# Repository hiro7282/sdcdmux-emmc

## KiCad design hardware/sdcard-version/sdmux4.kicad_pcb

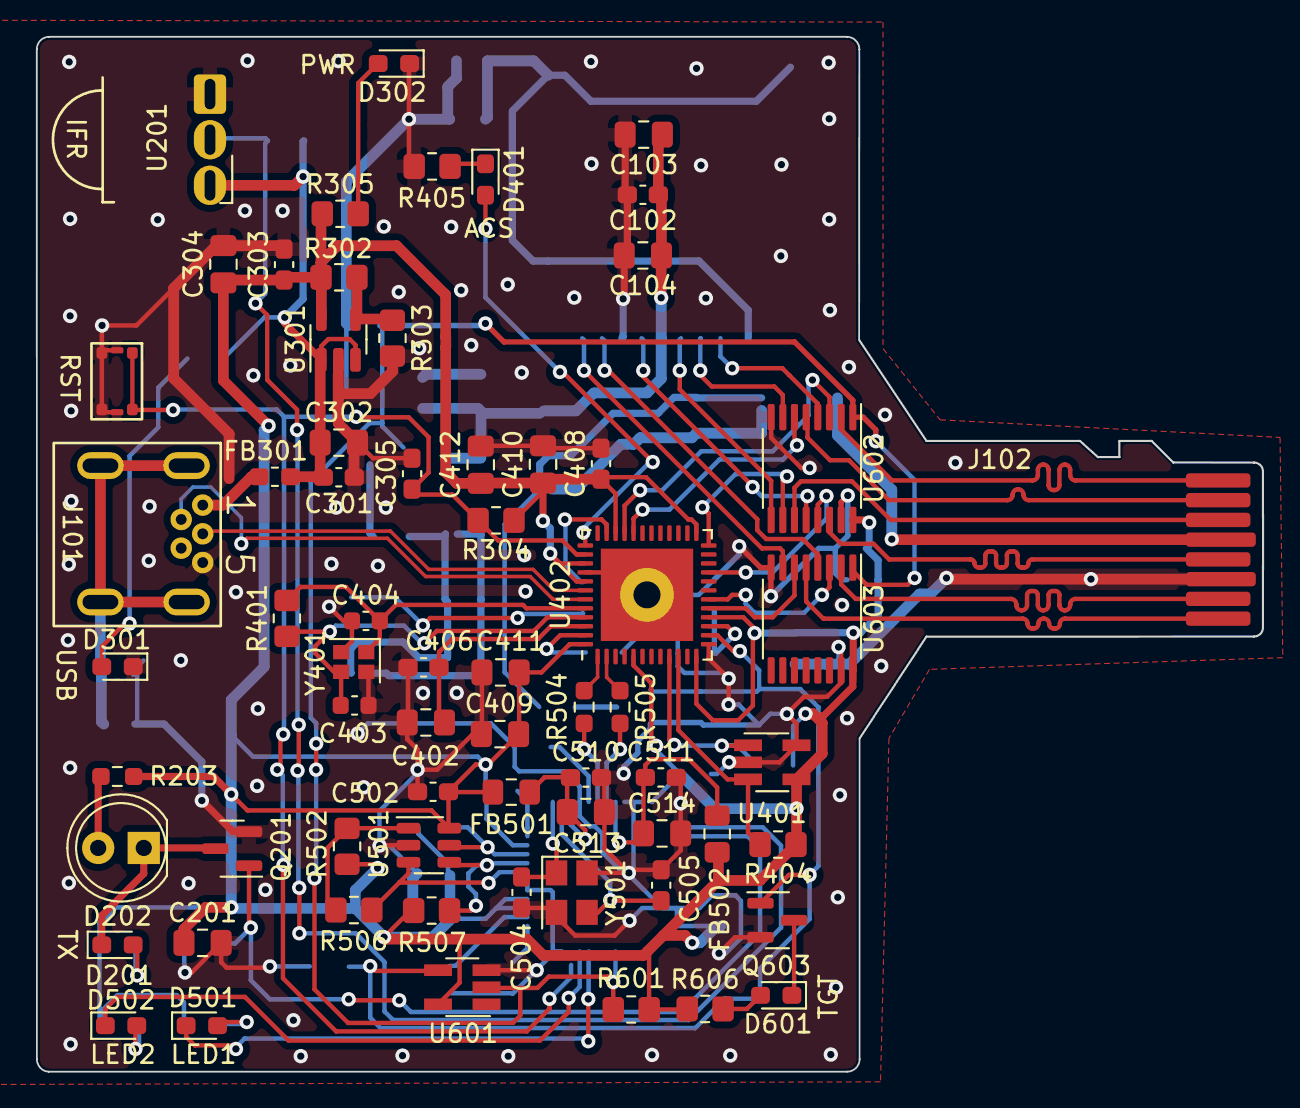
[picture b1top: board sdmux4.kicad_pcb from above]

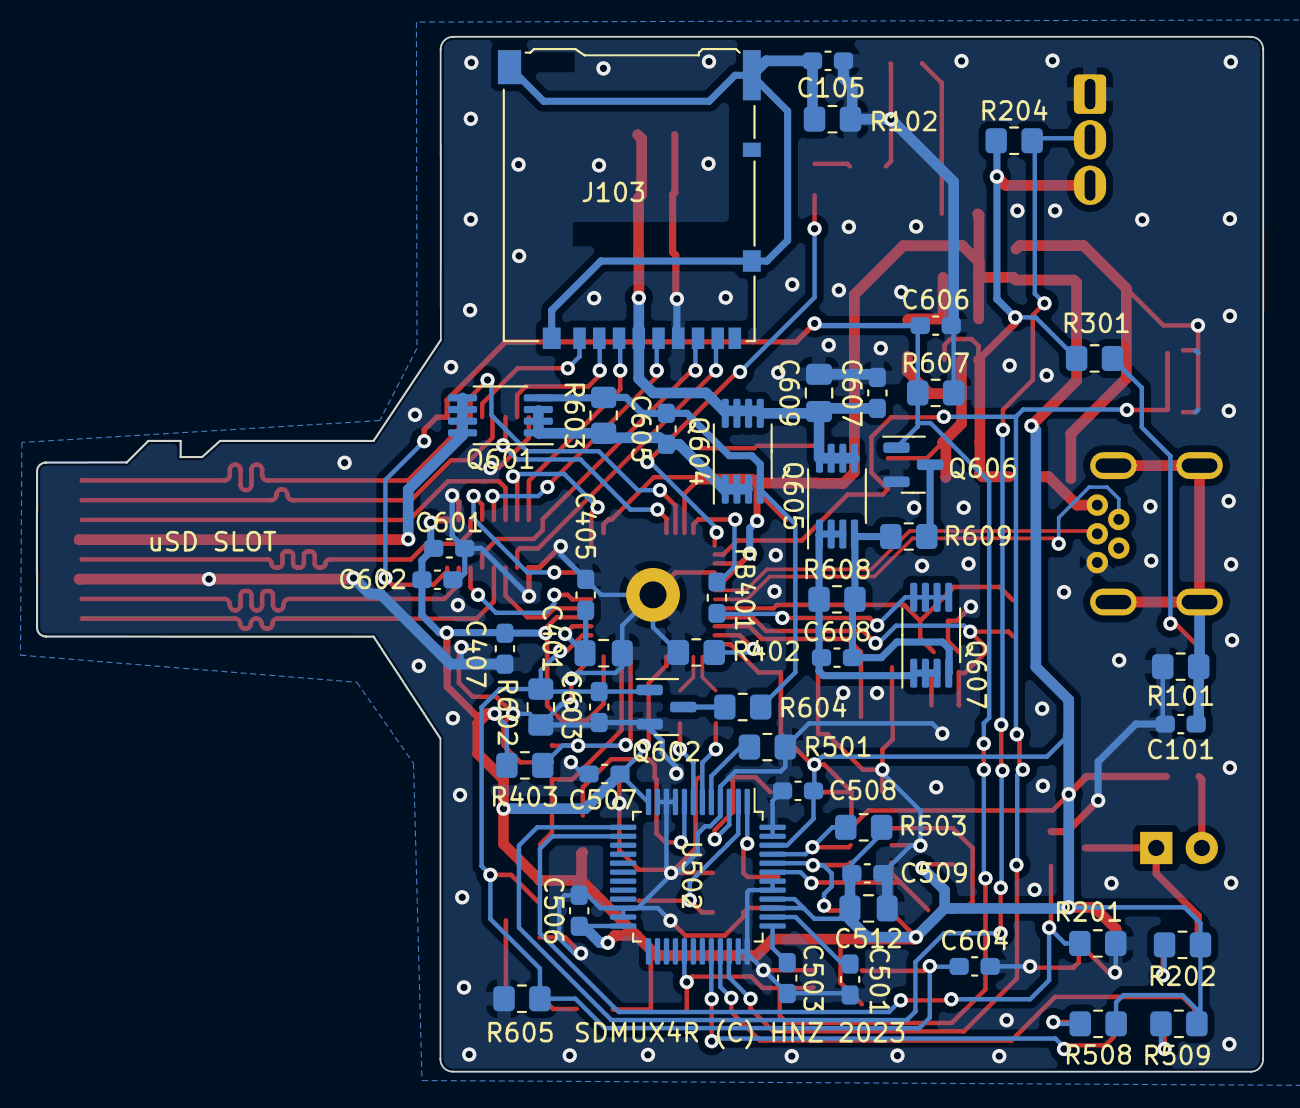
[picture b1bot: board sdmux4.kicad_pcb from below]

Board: 2 copper layers, 68.3 x 57.7 mm, 115 parts (49 on the bottom side), 77 nets.

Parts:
C101, C102, C105, C301, C303, C305, C405, C406, C407, C408, C501, C502, C503, C506, C507, C508, C509, C510, C511, C601, C602, C603, C604, C606, C607: 0.1uF/50v; C_0603_1608Metric_Pad1.08x0.95mm_HandSolder
C103, C401, C402, C409, C410: 1uF/10v; C_0805_2012Metric_Pad1.18x1.45mm_HandSolder
C104, C411, C412, C512, C513, C514: 4.7uF/50v; C_0805_2012Metric_Pad1.18x1.45mm_HandSolder
C201, C302, C304, C609: 10uF/16v; C_0805_2012Metric_Pad1.18x1.45mm_HandSolder
C403, C404: 27pF/50v; C_0603_1608Metric
C504, C505: 27pF/50v; C_0603_1608Metric_Pad1.08x0.95mm_HandSolder
C605, C608: 2.2uF/16v; C_0603_1608Metric_Pad1.08x0.95mm_HandSolder
D201, D301, D302, D401: LED RED; LED_0603_1608Metric_Pad1.05x0.95mm_HandSolder
D202: OSI5LA5113A; LED_D5.0mm
D501: IND-1 LED GRN; LED_0603_1608Metric_Pad1.05x0.95mm_HandSolder
D502: IND-2 LED GRN; LED_0603_1608Metric_Pad1.05x0.95mm_HandSolder
D601: TGT SEL LED RED; LED_0603_1608Metric_Pad1.05x0.95mm_HandSolder
FB301: BLM18KG601SN1D; L_0603_1608Metric_Pad1.05x0.95mm_HandSolder
FB401: BLM18RK102SN1; L_0603_1608Metric_Pad1.05x0.95mm_HandSolder
FB501, FB502: BK2125HS601-T; L_0805_2012Metric_Pad1.15x1.40mm_HandSolder
J101: USB_B_Mini; usb mini B connector c2235 dim 2
J102: uSD-CARD-PAD; uSD Card Pad
J103: Micro_SD_Card_Det_Hirose_DM3AT-SF-PEJM5; microSD_HC_Hirose_DM3AT-SF-PEJM5
Q201, Q602, Q603, Q606: 2N7002K; SOT-23
Q601, Q604, Q605, Q607: ZXM64P02XTA; MSOP-8_3x3mm_P0.65mm
R101, R102, R201, R204, R304, R403, R404, R502, R503, R507, R601, R602, R603, R605, R607, R608: 10K; R_0805_2012Metric_Pad1.20x1.40mm_HandSolder
R202, R301, R604, R606, R609: 1K; R_0805_2012Metric_Pad1.20x1.40mm_HandSolder
R203: 33R; R_0603_1608Metric_Pad0.98x0.95mm_HandSolder
R302: 20K 1%; R_0805_2012Metric_Pad1.20x1.40mm_HandSolder
R303, R402, R501: 12K 1%; R_0805_2012Metric_Pad1.20x1.40mm_HandSolder
R305: 330; R_0805_2012Metric_Pad1.20x1.40mm_HandSolder
R401: 1M; R_0805_2012Metric_Pad1.20x1.40mm_HandSolder
R405: 330R; R_0805_2012Metric_Pad1.20x1.40mm_HandSolder
R504, R505: 27R; R_0603_1608Metric_Pad0.98x0.95mm_HandSolder
R506: 2K; R_0805_2012Metric_Pad1.20x1.40mm_HandSolder
R508, R509: 220; R_0805_2012Metric_Pad1.20x1.40mm_HandSolder
SW301: 435151014824; WS-TASV SMT Tact Switch
U201: SPS-445; SPS445 3pin
U301: SPX3819M5-L; SOT-23-5
U401: AT24MAC402-STUM; SOT-23-5_HandSoldering
U402: USB2640-HZH-02; QFN-48-1EP_7x7mm_P0.5mm_EP5.15x5.15mm
U501: 93LCxxBxxOT; SOT-23-6
U502: FT232HL; LQFP-48_7x7mm_P0.5mm
U601: 74AHC1G14; SOT-23-5_HandSoldering
U602, U603: TMUX1574PWR; TSSOP-16_4.4x5mm_P0.65mm
Y401: 24MHz; Crystal_SMD_2016-4Pin_2.0x1.6mm
Y501: 12MHz; Crystal_SMD_3225-4Pin_3.2x2.5mm

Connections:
+3.3V: C201.1, C303.1, C304.1, C407.1, C408.1, C409.1, C410.1, C411.1, C412.1, C502.1, C506.1, C507.1, C508.1, C509.1, C512.1, C601.1, C602.1, FB501.1, FB502.1, R202.1, R203.1, R302.1, R304.1, R305.1, R403.1, R404.1, R502.1, R503.1, R507.1, R508.1, R509.1, R601.1, R606.1, U301.5 (OUT), U401.4 (VCC), U402.5 (VDD33), U402.12 (VDD33), U402.16 (VDD33), U402.25 (VDD33), U402.34 (VDD33), U402.39 (VBUS_DET), U402.41 (VDD33), U402.48 (VDD33), U501.6 (VCC), U502.12 (VCCIO), U502.24 (VCCIO), U502.39 (VCCD), U502.40 (VREGIN), U502.46 (VCCIO), U601.5 (VCC), U602.16 (VDD), U603.16 (VDD)
+5V: C301.1, C302.1, FB301.2, R204.1, R301.1, U201.3 (Vcc), U301.1 (IN), U301.3 (EN)
/Infrad Cont/INFRAD_RX: R204.2, U201.2 (Out), U502.13 (ADBUS0)
/Infrad Cont/INFRAD_TX: Q201.1 (G), R201.1, U502.14 (ADBUS1)
/SDCARD_READER/SD1: U402.33 (xD_D5/SD_D2), U602.3 (S1B)
/SDCARD_READER/SD2: U402.32 (xD_D6/SD_D3/MS_D3), U602.6 (S2B)
/SDCARD_READER/SD3: U402.24 (xD_CLE/SD_CMD/MS_D0), U602.10 (S3B)
/SDCARD_READER/SD4: FB401.2, Q607.5 (D), Q607.6 (D), Q607.7 (D), Q607.8 (D)
/SDCARD_READER/SD5: U402.21 (xD_nWP/SD_CLK/MS_BS), U602.13 (S4B)
/SDCARD_READER/SD7: U402.18 (xD_D2/SD_D0/MS_D4), U603.3 (S1B)
/SDCARD_READER/SD8: U402.17 (xD_D3/SD_D1/MS_D5), U603.6 (S2B)
/SDCARD_READER/SD9: C603.1, C604.1, Q602.1 (G), Q603.1 (G), R602.1, R605.1, U402.14 (SD_~CD), U601.4
/SDCARD_READER/USB+: J101.3 (D+), U402.42 (USB+)
/SDCARD_READER/USB-: J101.2 (D-), U402.43 (USB-)
/SDCARD_READER/USBDP1+: R505.1, U402.2 (USBDN_DP2)
/SDCARD_READER/USBDP1-: R504.1, U402.1 (USBDN_DM2)
/SDCARD_READER/~RESET: C305.1, R304.2, SW301.1, SW301.2, U402.38 (~RESET), U502.34 (~RESET)
/SDMUX/SD1_1: J102.1, U602.2 (S1A)
/SDMUX/SD1_2: J102.2, U602.5 (S2A)
/SDMUX/SD1_3: J102.3, U602.11 (S3A)
/SDMUX/SD1_4: J102.4, Q601.5 (D), Q601.6 (D), Q601.7 (D), Q601.8 (D)
/SDMUX/SD1_5: J102.5, U602.14 (S4A)
/SDMUX/SD1_7: J102.7, U603.2 (S1A)
/SDMUX/SD1_8: J102.8, U603.5 (S2A)
/SDMUX/SDOUT1: J103.1 (DAT2), U602.4 (D1)
/SDMUX/SDOUT2: J103.2 (DAT3/CD), U602.7 (D2)
/SDMUX/SDOUT3: J103.3 (CMD), U602.9 (D3)
/SDMUX/SDOUT4: C102.1, C103.1, C104.1, C607.1, C609.1, J103.4 (VDD), Q604.5 (D), Q604.6 (D), Q604.7 (D), Q604.8 (D), Q605.5 (D), Q605.6 (D), Q605.7 (D), Q605.8 (D)
/SDMUX/SDOUT5: J103.5 (CLK), U602.12 (D4)
/SDMUX/SDOUT7: J103.7 (DAT0), U603.4 (D1)
/SDMUX/SDOUT8: J103.8 (DAT1), U603.7 (D2)
/SDMUX/~SEL1: C606.1, Q606.1 (G), R601.2, R607.1, U502.29 (ACBUS5), U601.2, U602.1 (SEL), U603.1 (SEL)
/SELECTOR/ACBUS8: D501.1 (K), U502.32 (ACBUS8)
/SELECTOR/ACBUS9: D502.1 (K), U502.33 (ACBUS9)
/SELECTOR/VPHY: C510.1, C513.1, FB501.2, U502.3 (VPHY)
/SELECTOR/VPLL: C511.1, C514.1, FB502.2, U502.8 (VPLL)
/USB Power/USBVDD_5V: FB301.1, J101.1 (VBUS)
GND: C101.2, C102.2, C103.2, C104.2, C105.2, C201.2, C301.2, C302.2, C303.2, C304.2, C305.2, C401.2, C402.2, C403.1, C404.1, C405.2, C406.2, C407.2, C408.2, C409.2, C410.2, C411.2, C412.2, C501.2, C502.2, C503.2, C504.2, C505.2, C506.2, C507.2, C508.2, C509.2, C510.2, C511.2, C512.2, C513.2, C514.2, C601.2, C602.2, C603.2, C604.2, C606.2, C607.2, C609.2, D301.1 (K), D302.1 (K), J101.5 (GND), J102.6, J103.6 (VSS), Q201.2 (S), Q602.2 (S), Q603.2 (S), Q606.2 (S), R101.2, R102.2, R201.2, R303.2, R402.2, R405.2, R501.2, R602.2, R605.2, R607.2, SW301.3 (K), SW301.4 (A), SW301.5, SW301.6, U201.1 (GND), U301.2 (GND), U401.2 (GND), U401.5 (WP), U402.13 (xD_D4/SD_WP/MS_SCLK), U402.40 (TEST), U402.49 (VSS), U501.2 (GND), U502.4 (AGND), U502.9 (AGND), U502.10 (GND), U502.11 (GND), U502.22 (GND), U502.23 (GND), U502.35 (GND), U502.36 (GND), U502.41 (AGND), U502.42 (TEST), U502.47 (GND), U502.48 (GND), U601.3 (GND), U602.8 (GND), U602.15 (~EN), U603.8 (GND), U603.15 (~EN), Y401.2, Y401.4, Y501.2, Y501.4
unnamed: C605.1, Q601.1 (S), Q601.2 (S), Q601.3 (S), Q604.1 (S), Q604.2 (S), Q604.3 (S), R603.1
unnamed: C608.1, Q605.1 (S), Q605.2 (S), Q605.3 (S), Q607.1 (S), Q607.2 (S), Q607.3 (S), R608.1
unnamed: D201.2 (A), R202.2
unnamed: D201.1 (K), D202.1 (K), Q201.3 (D)
unnamed: D202.2 (A), R203.2
unnamed: D301.2 (A), R301.2
unnamed: D302.2 (A), R305.2
unnamed: D401.2 (A), U402.37 (LED)
unnamed: D401.1 (K), R405.1
unnamed: D501.2 (A), R508.2
unnamed: D502.2 (A), R509.2
unnamed: D601.2 (A), R606.2
unnamed: D601.1 (K), Q603.3 (D)
unnamed: C101.1, J101.6 (Shield), R101.1
unnamed: C105.1, J103.11 (SHIELD), R102.1
unnamed: C605.2, Q601.4 (G), Q604.4 (G), R603.2, R604.2
unnamed: Q602.3 (D), R604.1
unnamed: C608.2, Q605.4 (G), Q607.4 (G), R608.2, R609.2
unnamed: Q606.3 (D), R609.1
unnamed: R302.2, R303.1, U301.4 (ADJ)
unnamed: R403.2, U401.1 (SCL), U402.9 (SPI_CLK/SCL)
unnamed: R404.2, U401.3 (SDA), U402.10 (SPI_DO/SDA/SPI_SPD_SEL)
unnamed: FB401.1, U402.35 (CRD_PWR)
unnamed: C401.1, C405.1, U402.15 (CRFILT)
unnamed: C402.1, C406.1, U402.46 (PLLFILT)
unnamed: R402.1, U402.47 (RBIAS)
unnamed: C403.2, R401.1, U402.45 (XTAL1/CLKIN), Y401.3
unnamed: C404.2, R401.2, U402.44 (XTAL2), Y401.1
unnamed: R507.2, U501.4 (CLK), U502.44 (EECLK)
unnamed: R503.2, U501.5 (CS), U502.45 (EECS)
unnamed: R506.1, U501.3 (DI), U502.43 (EEDATA)
unnamed: R502.2, R506.2, U501.1 (DO)
unnamed: R504.2, U502.6 (DM)
unnamed: R505.2, U502.7 (DP)
unnamed: R501.1, U502.5 (REF)
unnamed: C503.1, U502.37 (VCCA)
unnamed: C501.1, U502.38 (VCCCORE)
unnamed: C504.1, U502.1 (XCSI), Y501.1
unnamed: C505.1, U502.2 (XCSO), Y501.3

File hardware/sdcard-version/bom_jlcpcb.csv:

Comment,Designator,Footprint,JLCPCB Part #（optional）
0.1uF/50v,"C101,C102,C105,C301,C303,C305,C405,C406,C407,C408,C501,C502,C503,C506,C507,C508,C509,C510,C511,C601,C602,C603,C604,C606,C607",C_0603_1608Metric_Pad1.08x0.95mm_HandSolder,C14663
1uF/10v,"C103,C401,C402,C409,C410",C_0805_2012Metric_Pad1.18x1.45mm_HandSolder,C28323
4.7uF/25v,"C104,C411,C412,C512,C513,C514",C_0805_2012Metric_Pad1.18x1.45mm_HandSolder,C1779
10uF/16v,"C201,C302,C304,C609",C_0805_2012Metric_Pad1.18x1.45mm_HandSolder,C15850
27pF/50v,"C403,C404",C_0603_1608Metric,C1656
27pF/50v,"C504,C505",C_0603_1608Metric_Pad1.08x0.95mm_HandSolder,C1656
2.2uF/16v,"C605,C608",C_0603_1608Metric_Pad1.08x0.95mm_HandSolder,C23630
LED RED,"D201,D301,D302,D401",LED_0603_1608Metric_Pad1.05x0.95mm_HandSolder,C2286
IND-1 LED GRN,D501,LED_0603_1608Metric_Pad1.05x0.95mm_HandSolder,C12624
IND-2 LED GRN,D502,LED_0603_1608Metric_Pad1.05x0.95mm_HandSolder,C12624
TGT SEL LED RED,D601,LED_0603_1608Metric_Pad1.05x0.95mm_HandSolder,C2286
BLM18KG601SN1D,FB301,L_0603_1608Metric_Pad1.05x0.95mm_HandSolder,C85833
BLM18RK102SN1,FB401,L_0603_1608Metric_Pad1.05x0.95mm_HandSolder,C88986
BK2125HS601-T,"FB501,FB502",L_0805_2012Metric_Pad1.15x1.40mm_HandSolder,C1017
Micro_SD_Card_Det_Hirose_DM3AT-SF-PEJM5,J103,microSD_HC_Hirose_DM3AT-SF-PEJM5,C114218
2N7002K,"Q201,Q602,Q603,Q606",SOT-23,C22379475
ZXM64P02XTA,"Q601,Q604,Q605,Q607",MSOP-8_3x3mm_P0.65mm,C445529
10K,"R101,R102,R201,R204,R304,R403,R404,R502,R503,R507,R601,R602,R603,R605,R607,R608",R_0805_2012Metric_Pad1.20x1.40mm_HandSolder,C17414
1K,"R202,R301,R604,R606,R609",R_0805_2012Metric_Pad1.20x1.40mm_HandSolder,C17513
33R,R203,R_0603_1608Metric_Pad0.98x0.95mm_HandSolder,C23140
20K 1%,R302,R_0805_2012Metric_Pad1.20x1.40mm_HandSolder,C4328
12K 1%,"R303,R402,R501",R_0805_2012Metric_Pad1.20x1.40mm_HandSolder,C17444
330,R305,R_0805_2012Metric_Pad1.20x1.40mm_HandSolder,C17630
1M,R401,R_0805_2012Metric_Pad1.20x1.40mm_HandSolder,C17514
330R,R405,R_0805_2012Metric_Pad1.20x1.40mm_HandSolder,C17630
27R,"R504,R505",R_0603_1608Metric_Pad0.98x0.95mm_HandSolder,C25190
2K,R506,R_0805_2012Metric_Pad1.20x1.40mm_HandSolder,C17604
220,"R508,R509",R_0805_2012Metric_Pad1.20x1.40mm_HandSolder,C17557
435151014824,SW301,WS-TASV SMT Tact Switch,C6418963
SPX3819M5-L,U301,SOT-23-5,C9056
AT24MAC402-STUM,U401,SOT-23-5_HandSoldering,C2061068
USB2640-HZH-02,U402,QFN-48-1EP_7x7mm_P0.5mm_EP5.15x5.15mm,C510950
93LCxxBxxOT,U501,SOT-23-6,C190271
FT232HL,U502,LQFP-48_7x7mm_P0.5mm,C51997
74AHC1G14,U601,SOT-23-5_HandSoldering,C176916
TMUX1574PWR,"U602,U603",TSSOP-16_4.4x5mm_P0.65mm,C2673443
24MHz,Y401,Crystal_SMD_2016-4Pin_2.0x1.6mm,C5155508
12MHz,Y501,Crystal_SMD_3225-4Pin_3.2x2.5mm,C9002
